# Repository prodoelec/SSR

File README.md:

# SSR

Interruptor de estado solido con paso por cero

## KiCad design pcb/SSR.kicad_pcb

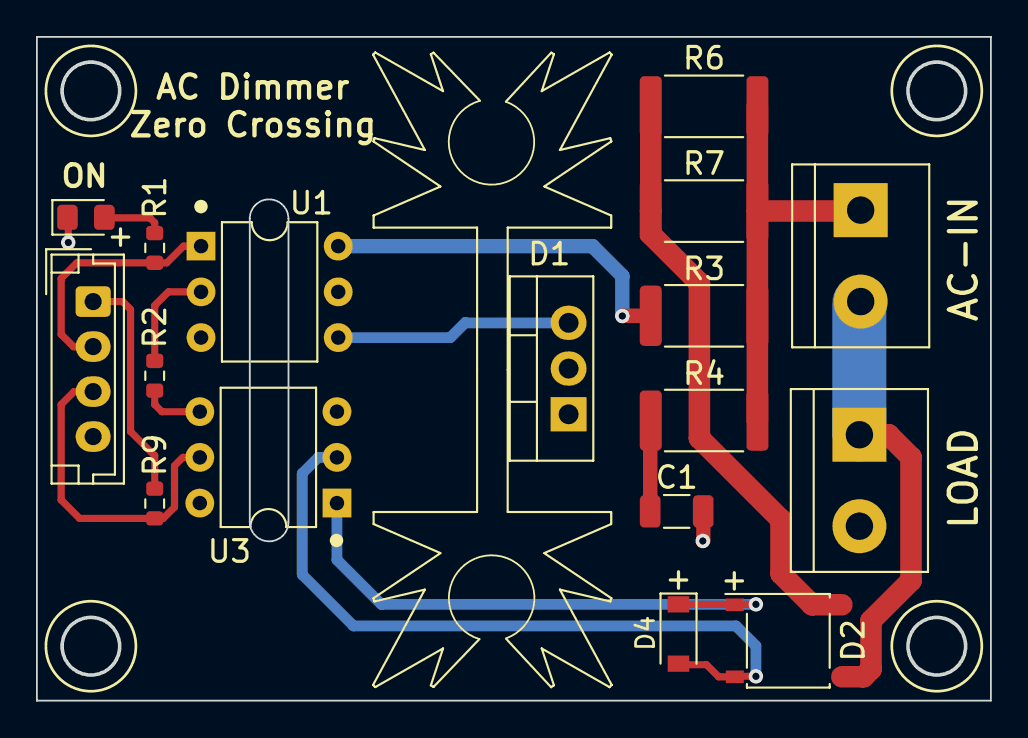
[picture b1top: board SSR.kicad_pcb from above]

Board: 2 copper layers, 52.9 x 36.8 mm, 18 parts (0 on the bottom side), 15 nets.

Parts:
C1: 10nF/400V; C_1206_3216Metric
D1: BTB10-800CWRG; TO-220-3_Vertical
D2: ABS8; Diode_Bridge_Diotec_ABS
D4: MMSZ4684-TP; D_SOD-123
HS1: Heatsink; Heatsink_Fischer_SK104-STC-STIC_35x13mm
J1: Conn_01x04; JST_EH_B4B-EH-A_1x04_P2.50mm_Vertical
J2: IN_AC; TerminalBlock_bornier-2_P5.08mm
J3: RESISTENCIA; TerminalBlock_bornier-2_P5.08mm
LD1: ON; LED_0805_2012Metric_Pad1.15x1.40mm_HandSolder
R1: 1K; R_0603_1608Metric
R2: 220; R_0603_1608Metric
R3: 1K; R_2512_6332Metric
R4: 39 *; R_2512_6332Metric
R6, R7: 120K; R_2512_6332Metric
R9: 10K; R_0603_1608Metric
U1: MOC3021M; DIP-6_W7.62mm
U3: 4N25; DIP-6_W7.62mm

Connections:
+5V: J1.1, R9.2
/CARGA: C1.2, D1.1 (A1), J3.2
/FASE: D1.2 (A2), J2.1, R3.2, R4.2, R6.2, R7.2
/NEUTRO: D2.3, J2.2, J3.1
/PWM: J1.2, R1.1, U1.1
GND: J1.4, LD1.1 (K), R2.1, U3.4
unnamed: C1.1, R4.1
unnamed: D1.3 (G), U1.4
unnamed: D2.1 (+), D4.1 (K), U3.1
unnamed: D2.2 (-), D4.2 (A), U3.2
unnamed: D2.4, R6.1, R7.1
unnamed: LD1.2 (A), R1.2
unnamed: R2.2, U1.2
unnamed: R3.1, U1.6
ZC: J1.3, R9.1, U3.5

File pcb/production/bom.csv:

Designator,Footprint,Quantity,Value,LCSC Part #
C1,C_1206_3216Metric,1,10nF/400V,
D1,TO-220-3_Vertical,1,BTB10-800CWRG,
D2,Diode_Bridge_Diotec_ABS,1,ABS8,
HS1,Heatsink_Fischer_SK104-STC-STIC_35x13mm,1,Heatsink,
J1,JST_EH_B4B-EH-A_1x04_P2.50mm_Vertical,1,Conn_01x04,
J2,TerminalBlock_bornier-2_P5.08mm,1,IN_AC,
J3,TerminalBlock_bornier-2_P5.08mm,1,RESISTENCIA,
LD1,LED_0805_2012Metric_Pad1.15x1.40mm_HandSolder,1,ON,
R1,R_0603_1608Metric,1,270,
R2,R_0603_1608Metric,1,330,
R3,R_2512_6332Metric,1,1K,
R4,R_2512_6332Metric,1,39 *,
"R6, R7",R_2512_6332Metric,2,120K,
R9,R_0603_1608Metric,1,10K,
U1,DIP-6_W7.62mm,1,MOC3021M,
U3,DIP-6_W7.62mm,1,4N25,

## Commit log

2023-02-06 original
2023-02-06 Readme
2023-02-06 imagen
2023-05-30 Añadido Zener
